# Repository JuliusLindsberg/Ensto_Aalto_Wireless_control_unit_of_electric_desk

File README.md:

# Wireless contol unit of electric desk
This is an Aalto University student project which aims to produce a functional prototype for a wireless controller of an electric desk. It is being developed
in collaboration with Ensto. Software will be published under a very permissive MIT license. See the licence file disclosed in this repository for details.
## Hardware
Our aim currently is to provide a working solution for only specific hardware. In our code there may or may not be useful generalizations for other types of
hardware choices too but quite certainly our solution is not going to work right out the box.
### Microcontroller: NRF52840
NRF52840 provides adequate support for bluetooth low energy and potential for control via NFC tags.
### Desk interface module
Module for interfacing between nrf52840 Dev Kit and Martela electric desk. Not necessarily compatible with other manufacturers. KiCad files included.
## Software

### Zephyr RTOS
Zephyr RTOS is an open source real time operating system which we use in this project. It provides some device bindings for the NRF52840.
There is also a fork of Zephyr maintained by Nordic Semiconductors which may have helpful examples. However, it unfortunately doesn't directly support NFR52840. 
https://github.com/nrfconnect/sdk-nrf
### C++
Programming language used is C++ or plain C. Not at all every feature of C++ is applicable due to constraints imposed by Zephyr OS.
See: https://docs.zephyrproject.org/1.9.0/kernel/other/cxx_support.html
### Our code
See doc/API.md for our API reference.
### Arduino table control folder
Contents of said folder don't have an active role in the project and are there just for storage purposes only. They were used to try out some concepts and
electrical circuits with a seperate arduino board simultaneously.
## Getting started
Developing and building our project should be not very different from building any other zephyr project. As a bit of a warning Zephyr's work enviroment
takes a lot of space (several gigabytes) from your hard drive.
Developing Zephyr programs should be possible with any major operating system but so far we have used only Linux so other enviroments are a case of untested waters.
### Setting up the work enviroment
In order to build our code follow these instructions:
https://docs.zephyrproject.org/latest/getting_started/index.html
Then clone this git repository inside the zephyrproject/zephyr folder. With a little tweaking it probably is possible to build the project ouside zephyr folder
too but just cloning this repository inside it seems to be the most convenient way available.
### Building our project
We use Zephyr's west tool to build our project in a similiar fashion as the tutorial above does. In order to build this project navigate to this
git repository in your shell and then execute:
```
west build -p auto -b nrf52840dk_nrf52840 ./
```

If your microcontroller is not NRF52840, then -b option should naturally be something else.
### Flashing into the microcontroller
```
west flash
```
should work just fine as with any other Zephyr project. flash command also tries to build the project if it isn't up to date. So the build command might be redundant for your workflow.

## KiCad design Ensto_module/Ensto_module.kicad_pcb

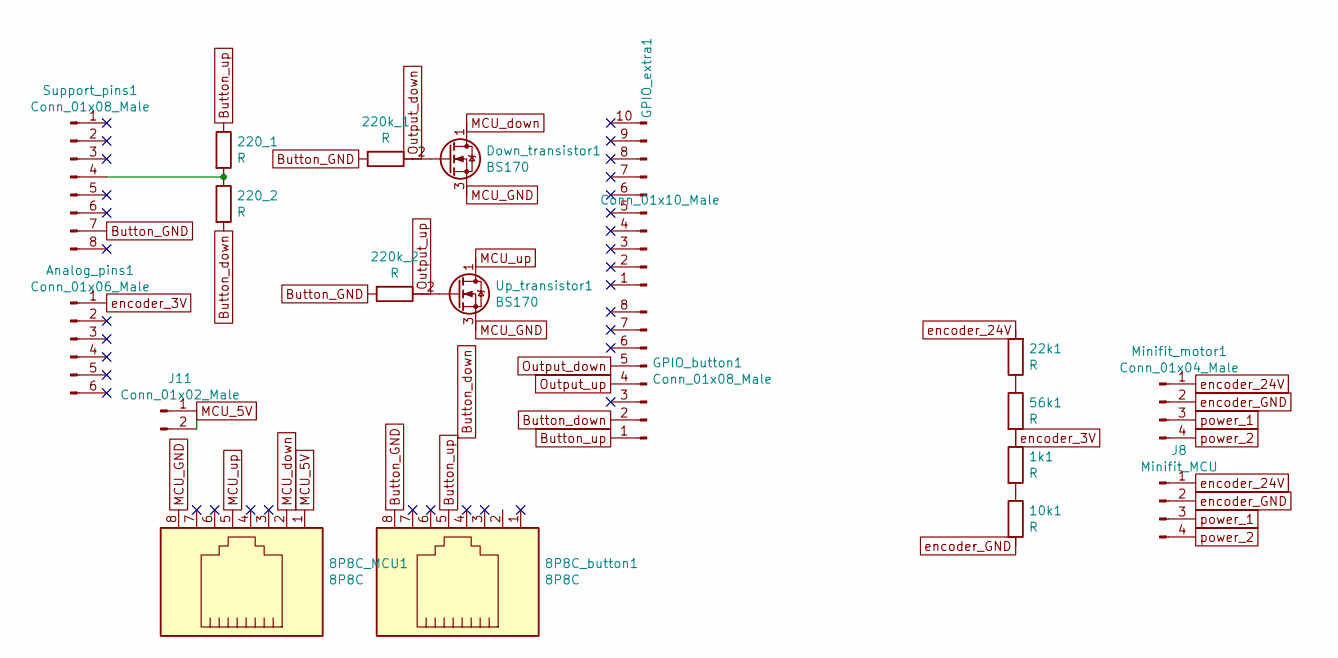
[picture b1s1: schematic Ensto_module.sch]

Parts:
1k1, 10k1, 22k1, 56k1, 220_1, 220_2, 220k_1, 220k_2: R; R_Axial_DIN0309_L9.0mm_D3.2mm_P15.24mm_Horizontal
8P8C_MCU1, 8P8C_button1: 8P8C; RJ45_Amphenol_54602-x08_Horizontal
Analog_pins1: Conn_01x06_Male; PinHeader_1x06_P2.54mm_Vertical
Down_transistor1: BS170; TO-92_Inline
GPIO_button1: Conn_01x08_Male; PinHeader_1x08_P2.54mm_Vertical
GPIO_extra1: Conn_01x10_Male; PinHeader_1x10_P2.54mm_Vertical
J8: Minifit_MCU; Molex_Mini-Fit_Jr_5569-04A2_2x02_P4.20mm_Horizontal
J11: Conn_01x02_Male; PinHeader_1x02_P2.54mm_Vertical
Minifit_motor1: Conn_01x04_Male; Molex_Mini-Fit_Jr_5569-04A2_2x02_P4.20mm_Horizontal
Support_pins1: Conn_01x08_Male; PinHeader_1x08_P2.54mm_Vertical
Up_transistor1: BS170; TO-92_Inline

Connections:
Button_GND: 8P8C_button1.8, 220k_1.2, 220k_2.2, Support_pins1.7
Button_down: 8P8C_button1.2, 220_2.2, GPIO_button1.2
Button_up: 8P8C_button1.5, 220_1.1, GPIO_button1.1
MCU_5V: 8P8C_MCU1.1, J11.1, J11.2
MCU_GND: 8P8C_MCU1.8, Down_transistor1.3 (S), Up_transistor1.3 (S)
MCU_down: 8P8C_MCU1.2, Down_transistor1.1 (D)
MCU_up: 8P8C_MCU1.5, Up_transistor1.1 (D)
unnamed: 1k1.2, 10k1.1
unnamed: 22k1.1, 56k1.1
unnamed: 220_1.2, 220_2.1, Support_pins1.4
Output_down: 220k_1.1, Down_transistor1.2 (G), GPIO_button1.5
Output_up: 220k_2.1, GPIO_button1.4, Up_transistor1.2 (G)
encoder_3V: 1k1.1, 56k1.2, Analog_pins1.1
encoder_24V: 22k1.2, J8.1, Minifit_motor1.1
encoder_GND: 10k1.2, J8.2, Minifit_motor1.2
power_1: J8.3, Minifit_motor1.3
power_2: J8.4, Minifit_motor1.4

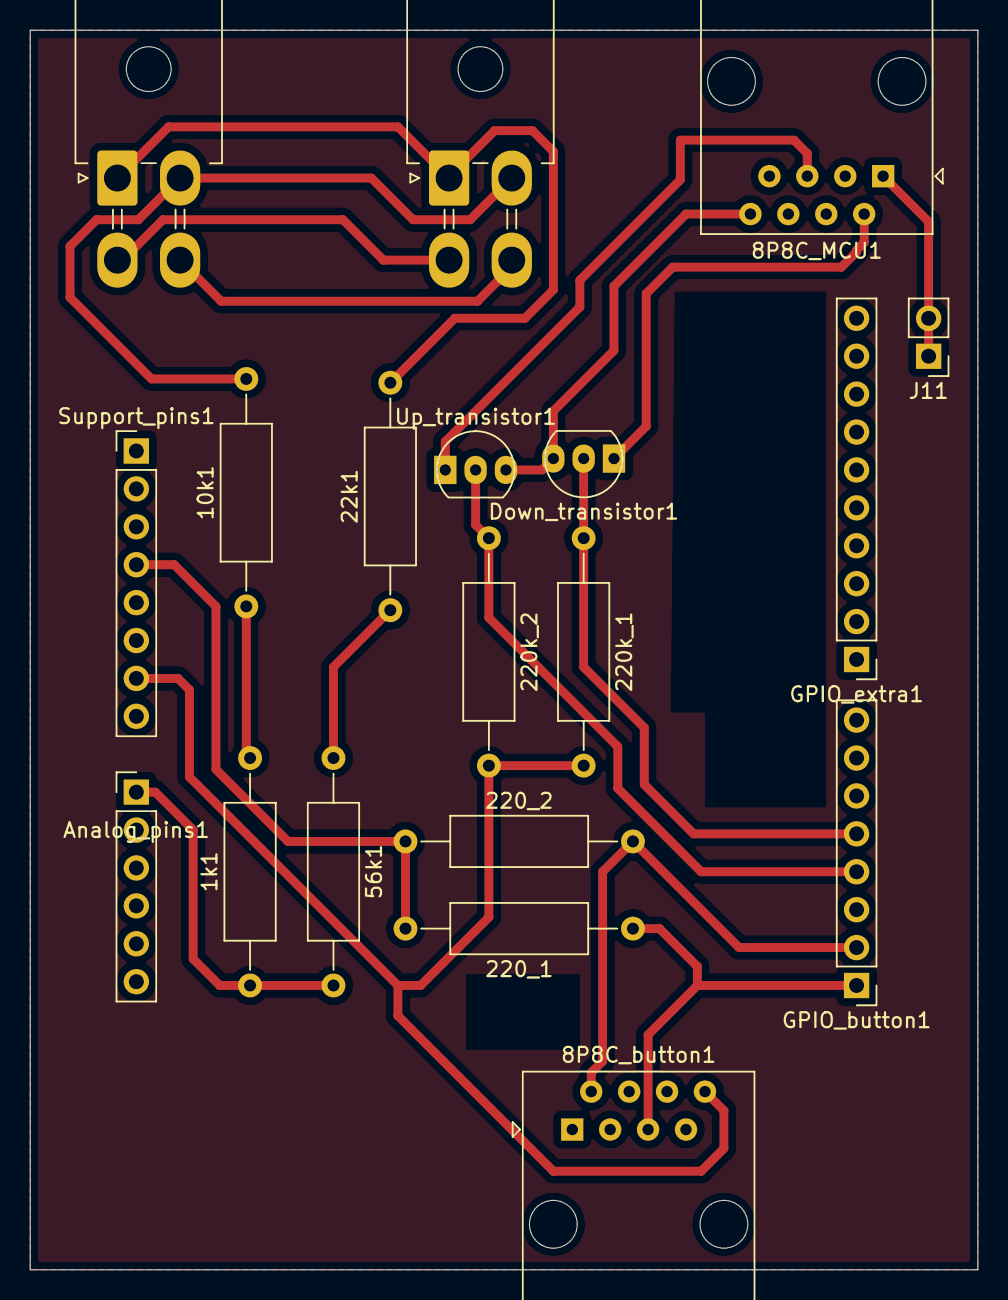
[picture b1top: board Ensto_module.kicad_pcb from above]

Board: 2 copper layers, 63.5 x 83.1 mm, 19 parts (0 on the bottom side), 17 nets.

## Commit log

2020-07-03 Added a basic concept of a file division, some documentation and a not-yet-functional but at least compiling class DebugBlinky.
2020-07-03 DebugBlinky class is now working as intended. Documentation not up to date.
2020-07-03 Updated API for DebugBlinker
2020-07-10 This commit is way too big...
2020-07-10 debugging functionality of EncoderAnalyzer and GPIO pins
2020-07-13 testing Zephyr's ADC library
2020-07-13 got EncoderAnalzer working-ish
2020-07-14 fixed md text formatting in README.md
2020-07-14 Fixed md formatting that was buggy.
2020-07-14 refactored SWO printing into a designated class with c++-like operator support.
2020-07-14 added related cpp and hpp files to bluetooth branch
2020-07-14 upstreaming bluetooth branch to remote
2020-07-14 added a new branch for developing encoder
2020-07-14 added support for reading samples
2020-07-14 Update EncoderAnalyzer.cpp
    Added encoder data analysis with 2 functions (analyzer and levelAnalyzer)
2020-07-14 Update EncoderAnalyzer.hpp
    Added encoder data analysis (analyze() and levelAnalyzer())
2020-07-14 minor tweaks to EncoderAnalyzer
2020-07-15 Did some cleanup on EncoderAnalyzer class and fixed behavior in other classes
2020-07-15 fixed main.cpp from merge conflict
2020-07-16 Added some debugging data to be printed for calibration
2020-07-16 configured raw thresholds
2020-07-16 made MotorController compatible with steering signals coming from from bt
2020-07-16 commented out non-compiling code for encoder and master branch
2020-07-16 commented out some more core...
2020-07-17 un-ruined master branch.
2020-07-17 Revert "un-ruined master branch."
    This reverts commit b874a9f5906d5917e943144e58ad4893c775bcc7.
2020-07-17 Revert "commented out non-compiling code for encoder and master branch"
    This reverts commit 22ffca109a7894fbcfb8070cc9c8c28147676f8e.
2020-07-20 replicated a zephyr sample bluetooth functionality in c++ without helper macros
2020-07-24 Fixed a typo
2020-07-24 made a few advancements to support a connectable active beacon for bluetooth
2020-07-27 Updated some of the documentation and removed useless virtual led concept
2020-07-29 trying to debug why beacon behavior doesn't work
2020-07-29 fixed DebugBlinker.hpp
2020-07-30 created a basic type of finite state machine to MotorController
2020-07-31 implemented button control successfully (untested in exceptional conditions)
2020-08-06 defining a custom GATT service for bluetooth low-energy
2020-08-06 Added a template android app in directory AndroidBLECentralApp
2020-08-06 added android project files to commit. It just seems to be easier that way...
2020-08-06 Revert adding android project files. The app will be in a completely seperate git repo
    This reverts commit 585cb8026e4a68d40b59355093dea7a077a9e726.
2020-08-06 Revert "Added a template android app in directory AndroidBLECentralApp". It will be in it's own seperate git repo
    This reverts commit 97d459e7415bbc71bd2827884f28407ae36e6176.
2020-08-07 updated a comment
2020-08-07 switching a branch
2020-08-07 removed the debug 'bluetooth' steer instruction from beginning
2020-08-17 BluetoothModule's gatt service interface 'works' now
2020-08-18 tweaked some minor values
2020-08-18 streamlined the bluetooth interface a bit
2020-08-19 minor adjustment
2020-08-19 removed useless kernel sleep after reset
2020-08-31 Add files via upload
    KiCad files for Bluetooth module.
2020-09-06 Add files via upload
    Added Control Box 3D-model upper and lower part files.
